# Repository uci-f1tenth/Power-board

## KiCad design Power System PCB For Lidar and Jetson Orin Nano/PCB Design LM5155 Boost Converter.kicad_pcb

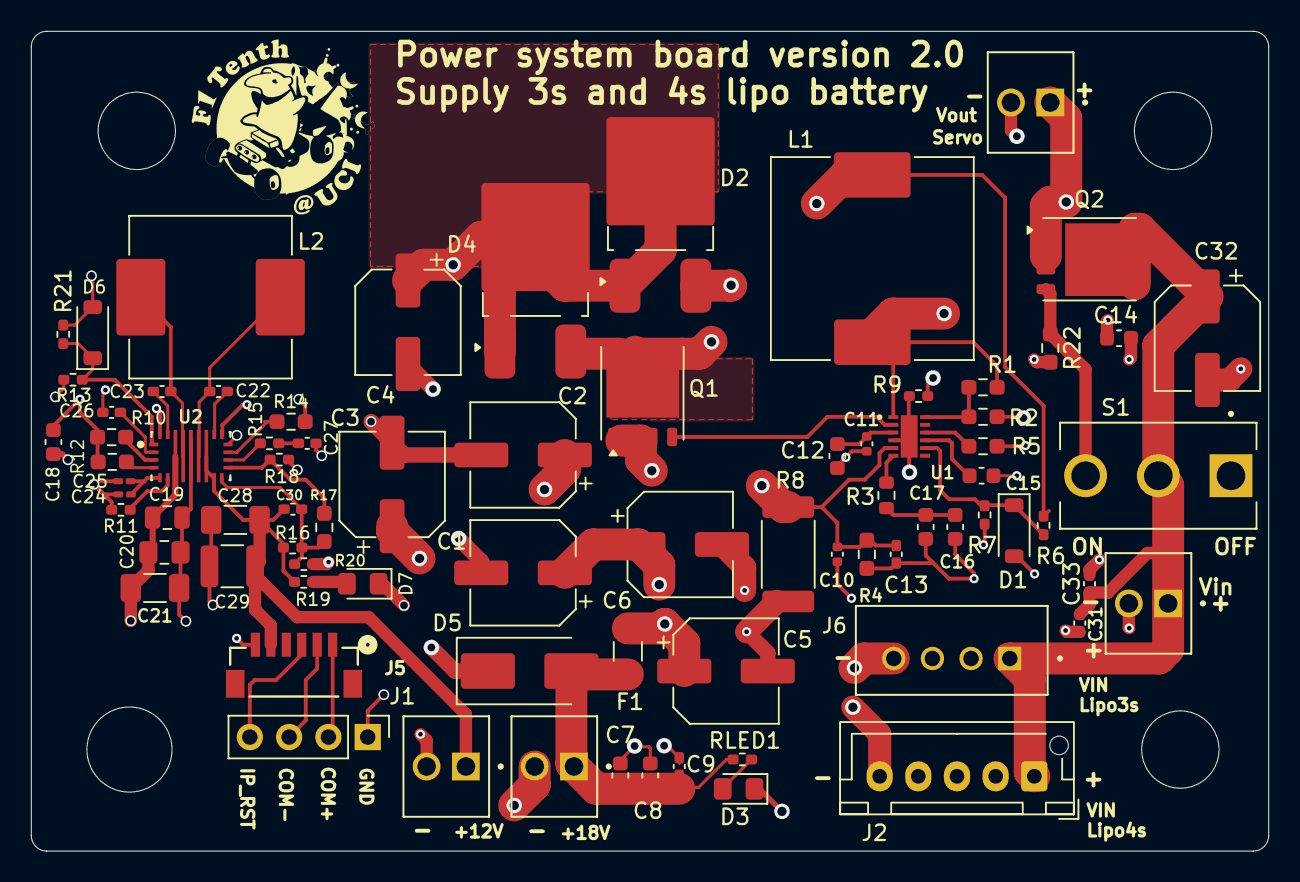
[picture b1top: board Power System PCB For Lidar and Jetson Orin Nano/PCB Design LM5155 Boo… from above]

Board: 4 copper layers, 80.0 x 53.0 mm, 80 parts (0 on the bottom side), 39 nets.

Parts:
+12V, +18V: TB002-500-02BE; TE_282834-2
C1, C2, C3, C4, C5, C6, C32: 100u; CP_Elec_6.3x5.8
C7, C14: 10u; C_0603_1608Metric
C8: 1.5u; C_0603_1608Metric
C9, C22, C23, C30, C31: 0.1u; C_0402_1005Metric_Pad0.74x0.62mm_HandSolder
C10, C11: 1u; C_0402_1005Metric
C12: 0.1u; C_0603_1608Metric
C13: 820p; C_0402_1005Metric_Pad0.74x0.62mm_HandSolder
C15: 0.15u; C_0603_1608Metric
C16: 220n; C_0603_1608Metric
C17: 680p; C_0603_1608Metric
C18: 4.7u; C_0603_1608Metric
C19: 10u; C_0805_2012Metric
C20: 10u; C_0805_2012Metric_Pad1.18x1.45mm_HandSolder
C21, C28: 22u; C_1206_3216Metric_Pad1.33x1.80mm_HandSolder
C24: 470p; C_0201_0603Metric_Pad0.64x0.40mm_HandSolder
C25: 6.8n; C_0201_0603Metric_Pad0.64x0.40mm_HandSolder
C26: 100p; C_0402_1005Metric_Pad0.74x0.62mm_HandSolder
C27, C33: 4.7n; C_0402_1005Metric_Pad0.74x0.62mm_HandSolder
C29: 47u; C_1210_3225Metric
D1: D_Zener; D_SOD-123
D2, D4: D_Schottky; TO-252-2_TabPin1
D3, D7: LED; LED_0805_2012Metric_Pad1.15x1.40mm_HandSolder
D5: D_TVS; D_SMB_Handsoldering
D6: 3.3; D_SOD-123
F1: Fuse; Fuse_1206_3216Metric_Pad1.42x1.75mm_HandSolder
J1: Conn_01x04_Pin; PinHeader_1x04_P2.54mm_Vertical
J2: B5B-XH-A; JST_XH_B5B-XH-AM_1x05_P2.50mm_Vertical
J5: BM06B-SRSS-TBLFSN; CONN_BM06B-SRSS-TB_JST
J6: B4B-XH-A; JST_B4B-XH-A
L1: 10u; L_Vishay_IHLP-5050
L2: 4.7u; L_Vishay_IHLP-4040
Q1, Q2: BSC035N04LS G; Infineon_PG-TDSON-8_6.15x5.15mm
R1: 226k; R_0603_1608Metric_Pad0.98x0.95mm_HandSolder
R2: 64.9k; R_0603_1608Metric_Pad0.98x0.95mm_HandSolder
R3: 1.2k; R_0603_1608Metric
R4: 100; R_0603_1608Metric_Pad0.98x0.95mm_HandSolder
R5: 44.8k; R_0603_1608Metric_Pad0.98x0.95mm_HandSolder
R6: 340k; R_0402_1005Metric_Pad0.72x0.64mm_HandSolder
R7: 20k; R_0402_1005Metric_Pad0.72x0.64mm_HandSolder
R8: 15m; R_2512_6332Metric_Pad1.40x3.35mm_HandSolder
R9: 0; R_0402_1005Metric_Pad0.72x0.64mm_HandSolder
R10, R12, R17, R22: 100k; R_0603_1608Metric_Pad0.98x0.95mm_HandSolder
R11: 50k; R_0402_1005Metric_Pad0.72x0.64mm_HandSolder
R13: 3.3k; R_0402_1005Metric_Pad0.72x0.64mm_HandSolder
R14: 150k; R_0603_1608Metric_Pad0.98x0.95mm_HandSolder
R15: 10k; R_0402_1005Metric_Pad0.72x0.64mm_HandSolder
R16: 10m; R_0402_1005Metric_Pad0.72x0.64mm_HandSolder
R18: 11k; R_0402_1005Metric_Pad0.72x0.64mm_HandSolder
R19: 1k; R_0402_1005Metric_Pad0.72x0.64mm_HandSolder
R20: 3; R_0402_1005Metric_Pad0.72x0.64mm_HandSolder
R21: 698; R_0402_1005Metric_Pad0.72x0.64mm_HandSolder
RLED1: 4k; R_0402_1005Metric_Pad0.72x0.64mm_HandSolder
Ref: LOGO; F1TenthUCILogo
S1: 100SP1T1B4M2QE; SW_100SP1T1B4M2QE
U1: LM5155_DSSR; WSON_551DSSR_TEX
U2: TPS552892RYQR; RYQ0021A-MFG
Vin: TB002-500-02BE; TE_282834-2
Vout: TB002-500-02BE; TE_282834-2

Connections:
/COUT: C1.1, C2.1, C3.1, C4.1, C5.1, C6.1, C19.1, C20.1, C21.1, D2.1 (K), D4.1 (K), F1.1, R13.1, U2.7 (VIN)
/INDUCTOR: C14.1, L1.1, Q2.1 (SOURCE), Q2.2 (SOURCE), Q2.3 (SOURCE), R1.2, R22.2, U1.1 (BIAS), Vout.1
/MOSFET: D2.2 (A), D4.2 (A), L1.2, Q1.5 (DRAIN), R6.1
/RSENSE: C10.1, C13.1, Q1.1 (SOURCE), Q1.2 (SOURCE), Q1.3 (SOURCE), R4.2, R8.1, U1.5 (CS)
/VIN: C31.1, C32.1, C33.1, J2.1, J6.1, Q2.5 (DRAIN), S1.2, Vin.1
/Vout2: +12V.1, C28.1, C29.1, C30.1, J5.5, R16.1, R19.1, U2.11 (VOUT), U2.12 (ISP)
GND: C11.2, C12.2, C13.2, C15.2, C16.2, C17.2, C18.1, C24.2, C25.2, C26.2, C27.2, D1.2 (A), R2.2, R4.1, R5.2, R7.2, R9.1, R11.2, R14.2, R18.2, R20.2, U2.17 (AGND), U2.21 (EXTVCC)
GNDPWR: +12V.2, +18V.2, C1.2, C2.2, C3.2, C4.2, C5.2, C6.2, C7.2, C8.2, C9.2, C10.2, C14.2, C19.2, C20.2, C21.2, C28.2, C29.2, C31.2, C32.2, C33.2, D3.1 (K), D5.1 (A1), D6.2 (A), D7.1 (K), J1.1, J2.5, J5.6, J6.4, R8.2, R9.2, R21.2, U1.4 (PGND), U1.13 (EP), U2.9 (PGND), Vin.2, Vout.2
unnamed: C16.1, C17.1, R3.1
unnamed: C27.1, R15.2
unnamed: D1.1 (K), R6.2, R7.1, U1.8 (FB)
unnamed: D3.2 (A), RLED1.1
unnamed: +18V.1, C7.1, C8.1, C9.1, D5.2 (A2), F1.2, RLED1.2
unnamed: D6.1 (K), R13.2, R21.1, U2.1 (EN_UVLO)
unnamed: D7.2 (A), R19.2
unnamed: J1.2, J5.1
unnamed: J1.3, J5.2
unnamed: J1.4, J5.3
unnamed: Q1.4 (GATE), U1.2 (GATE)
unnamed: Q2.4 (GATE), R22.1, S1.3
unnamed: R3.2, U1.6 (COMP)
unnamed: R5.1, U1.10 (RT)
unnamed: C15.1, U1.9 (SS)
unnamed: R1.1, R2.1, U1.12 (UVLO/SYNC)
unnamed: C11.1, C12.1, U1.3 (VCC)
unnamed: C23.2, U2.20 (BOOT1)
unnamed: C22.2, U2.19 (BOOT2)
unnamed: R12.2, U2.4 (CC_N)
unnamed: R14.1, U2.16 (CDC)
unnamed: R15.1, U2.15 (COMP)
unnamed: C24.1, C25.1, U2.5 (DITH_SYNC)
unnamed: R17.2, R18.1, U2.14 (FB)
unnamed: R11.1, U2.6 (FSW)
unnamed: C30.2, R16.2, R17.1, R20.1, U2.13 (ISN)
unnamed: C26.1, U2.2 (MODE)
unnamed: R10.2, U2.3 (PG)
unnamed: C23.1, L2.1, U2.8 (SW1)
unnamed: C22.1, L2.2, U2.10 (SW2)
unnamed: C18.2, R10.1, R12.1, U2.18 (VCC)

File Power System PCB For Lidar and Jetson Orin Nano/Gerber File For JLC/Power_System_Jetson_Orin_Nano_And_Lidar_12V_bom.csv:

Designator,Footprint,Quantity,Value,LCSC Part #
"+12V, +18V, VIN, VOUT",TE_282834-2,4,TB002-500-02BE,
"C1, C2, C3, C32, C4, C5, C6",CP_Elec_6.3x5.8,7,100u,
"C10, C11",0402,2,1u,
C12,0603,1,0.1u,
C13,0402,1,820p,
"C14, C7",0603,2,10u,
C15,0603,1,0.15u,
C16,0603,1,220n,
C17,0603,1,680p,
C18,0603,1,4.7u,
"C19, C20",0805,2,10u,
"C21, C28",1206,2,22u,
"C22, C23, C30, C31, C9",0402,5,0.1u,
C24,0201,1,470p,
C25,0201,1,6.8n,
C26,0402,1,100p,
"C27, C33",0402,2,4.7n,
C29,1210,1,47u,
C8,0603,1,1.5u,
D1,D_SOD-123,1,D_Zener,
"D2, D4",TO-252-2_TabPin1,2,D_Schottky,
"D3, D7",0805,2,LED,
D5,D_SMB_Handsoldering,1,D_TVS,
D6,D_SOD-123,1,3.3,
F1,1206,1,Fuse,
J1,PinHeader_1x04_P2.54mm_Vertical,1,Conn_01x04_Pin,
J2,JST_XH_B5B-XH-AM_1x05_P2.50mm_Vertical,1,B5B-XH-A,
J5,CONN_BM06B-SRSS-TB_JST,1,BM06B-SRSS-TBLFSN,
J6,JST_B4B-XH-A,1,B4B-XH-A,
L1,L_Vishay_IHLP-5050,1,10u,
L2,L_Vishay_IHLP-4040,1,4.7u,
"Q1, Q2",Infineon_PG-TDSON-8_6.15x5.15mm,2,BSC035N04LS G,
R1,0603,1,226k,
"R10, R12, R17, R22",0603,4,100k,
R11,0402,1,50k,
R13,0402,1,3.3k,
R14,0603,1,150k,
R15,0402,1,10k,
R16,0402,1,10m,
R18,0402,1,11k,
R19,0402,1,1k,
R2,0603,1,64.9k,
R20,0402,1,3,
R21,0402,1,698,
R3,0603,1,1.2k,
R4,0603,1,100,
R5,0603,1,44.8k,
R6,0402,1,340k,
R7,0402,1,20k,
R8,2512,1,15m,
R9,0402,1,0,
RLED1,0402,1,4k,
S1,SW_100SP1T1B4M2QE,1,100SP1T1B4M2QE,
U1,WSON_551DSSR_TEX,1,LM5155_DSSR,
U2,RYQ0021A-MFG,1,TPS552892RYQR,

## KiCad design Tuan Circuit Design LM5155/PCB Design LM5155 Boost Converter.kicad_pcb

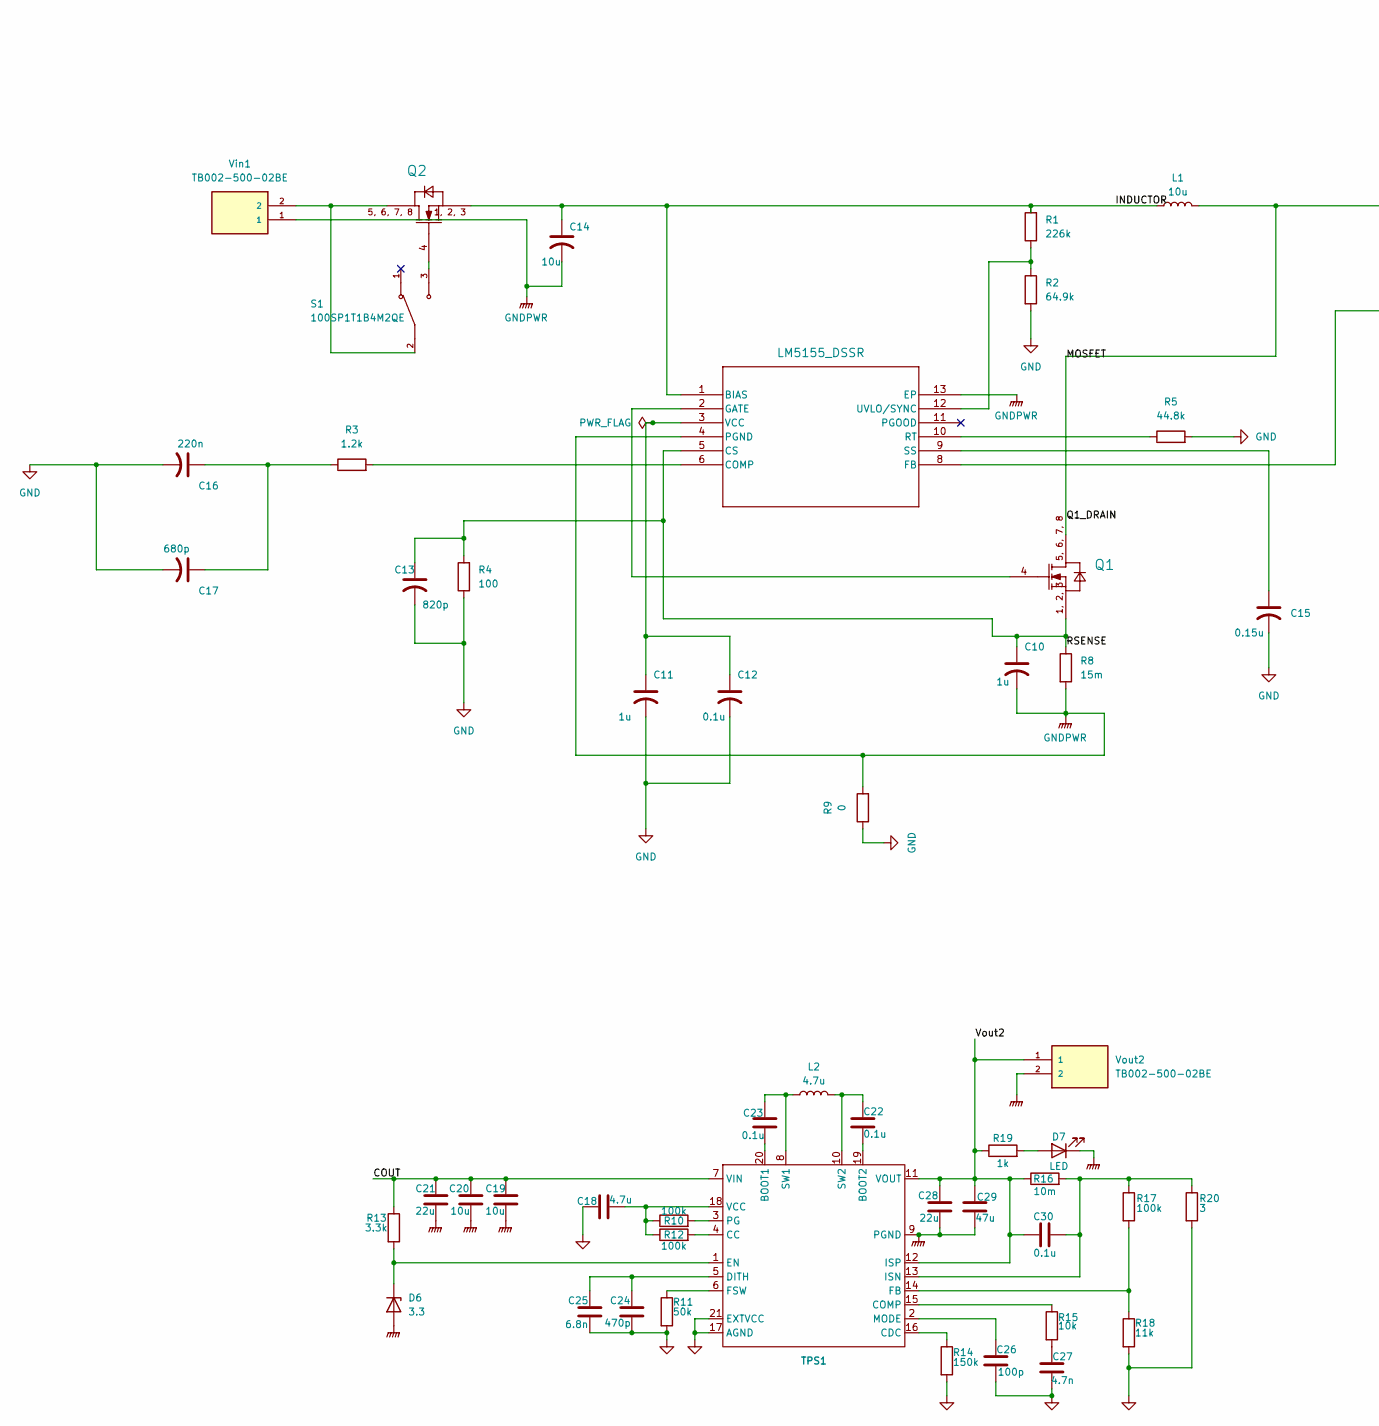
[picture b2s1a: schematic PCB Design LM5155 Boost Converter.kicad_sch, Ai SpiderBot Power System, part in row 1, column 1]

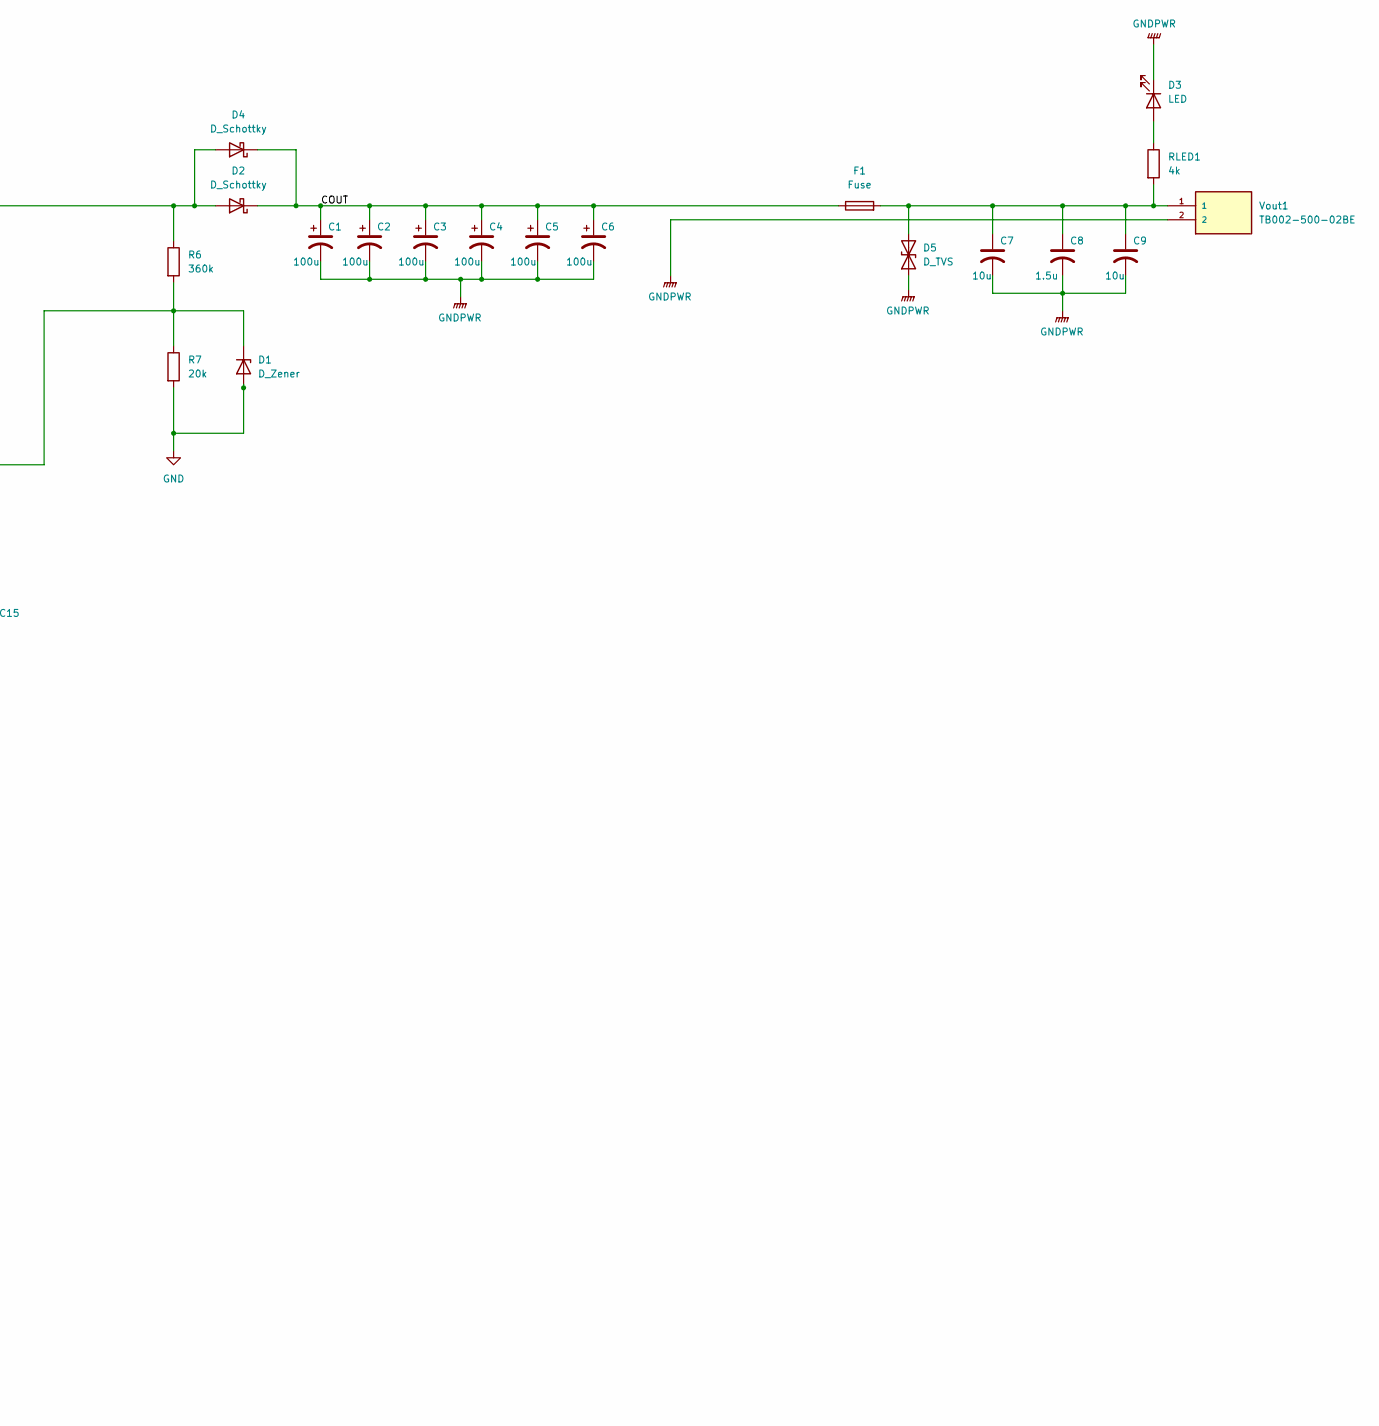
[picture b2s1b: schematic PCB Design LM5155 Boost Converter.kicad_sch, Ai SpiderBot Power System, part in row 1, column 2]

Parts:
C1, C2, C3, C4, C5, C6: 100u; CP_Elec_6.3x5.8
C7, C9, C14: 10u; C_0603_1608Metric
C8: 1.5u; C_0603_1608Metric
C10, C11: 1u; C_0402_1005Metric
C12: 0.1u; C_0603_1608Metric
C13: 820p; C_0402_1005Metric_Pad0.74x0.62mm_HandSolder
C15: 0.15u; C_0603_1608Metric
C16: 220n; C_0603_1608Metric
C17: 680p; C_0603_1608Metric
C18: 4.7u; C_0603_1608Metric
C19: 10u; C_0805_2012Metric
C20: 10u; C_0805_2012Metric_Pad1.18x1.45mm_HandSolder
C21, C28: 22u; C_1206_3216Metric_Pad1.33x1.80mm_HandSolder
C22, C23, C30: 0.1u; C_0402_1005Metric_Pad0.74x0.62mm_HandSolder
C24: 470p; C_0201_0603Metric_Pad0.64x0.40mm_HandSolder
C25: 6.8n; C_0201_0603Metric_Pad0.64x0.40mm_HandSolder
C26: 100p; C_0402_1005Metric_Pad0.74x0.62mm_HandSolder
C27: 4.7n; C_0402_1005Metric_Pad0.74x0.62mm_HandSolder
C29: 47u; C_1210_3225Metric
D1: D_Zener; D_SOD-123
D2, D4: D_Schottky; TO-252-2_TabPin1
D3, D7: LED; LED_0805_2012Metric_Pad1.15x1.40mm_HandSolder
D5: D_TVS; D_SMB_Handsoldering
D6: 3.3; D_SOD-123
F1: Fuse; Fuse_1206_3216Metric_Pad1.42x1.75mm_HandSolder
L1: 10u; L_Vishay_IHLP-5050
L2: 4.7u; L_Vishay_IHLP-4040
Q1, Q2: BSC035N04LS G; INF-PG-TDSON-8; ManufacturerPartNumber BSC035N04LS G
R1: 226k; R_0603_1608Metric_Pad0.98x0.95mm_HandSolder
R2: 64.9k; R_0603_1608Metric_Pad0.98x0.95mm_HandSolder
R3: 1.2k; R_0603_1608Metric
R4: 100; R_0603_1608Metric_Pad0.98x0.95mm_HandSolder
R5: 44.8k; R_0603_1608Metric_Pad0.98x0.95mm_HandSolder
R6: 360k; R_0402_1005Metric_Pad0.72x0.64mm_HandSolder
R7: 20k; R_0402_1005Metric_Pad0.72x0.64mm_HandSolder
R8: 15m; R_2512_6332Metric_Pad1.40x3.35mm_HandSolder
R9: 0; R_0402_1005Metric_Pad0.72x0.64mm_HandSolder
R10, R12, R17: 100k; R_0603_1608Metric_Pad0.98x0.95mm_HandSolder
R11: 50k; R_0402_1005Metric_Pad0.72x0.64mm_HandSolder
R13: 3.3k; R_0402_1005Metric_Pad0.72x0.64mm_HandSolder
R14: 150k; R_0603_1608Metric_Pad0.98x0.95mm_HandSolder
R15: 10k; R_0402_1005Metric_Pad0.72x0.64mm_HandSolder
R16: 10m; R_0402_1005Metric_Pad0.72x0.64mm_HandSolder
R18: 11k; R_0402_1005Metric_Pad0.72x0.64mm_HandSolder
R19: 1k; R_0402_1005Metric_Pad0.72x0.64mm_HandSolder
R20: 3; R_0402_1005Metric_Pad0.72x0.64mm_HandSolder
RLED1: 4k; R_0402_1005Metric_Pad0.72x0.64mm_HandSolder
S1: 100SP1T1B4M2QE; SW_100SP1T1B4M2QE; PARTREV E
TPS1: CONV_TPS552892RYQR
U1: LM5155_DSSR; WSON_551DSSR_TEX
Vin1: TB002-500-02BE; CUI_TB002-500-02BE
Vout1, Vout2: TB002-500-02BE; CUI_TB002-500-02BE

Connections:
/COUT: C1.1, C2.1, C3.1, C4.1, C5.1, C6.1, C19.1, C20.1, C21.1, D2.1 (K), D4.1 (K), F1.1, R13.1, TPS1.7 (VIN)
/INDUCTOR: C14.1, L1.1, Q2.1 (SOURCE), Q2.2 (SOURCE), Q2.3 (SOURCE), R1.2, U1.1 (BIAS)
/MOSFET: D2.2 (A), D4.2 (A), L1.2, Q1.5 (DRAIN), Q1.6 (DRAIN), Q1.7 (DRAIN), Q1.8 (DRAIN), R6.1
/RSENSE: C10.1, C13.1, Q1.1 (SOURCE), Q1.2 (SOURCE), Q1.3 (SOURCE), R4.2, R8.1, U1.5 (CS)
/Vout2: C28.1, C29.1, C30.1, R16.1, R19.1, TPS1.11 (VOUT), TPS1.12 (ISP), Vout2.1
GND: C11.2, C12.2, C13.2, C15.2, C16.2, C17.2, C18.1, C24.2, C25.2, C26.2, C27.2, D1.2 (A), R2.2, R4.1, R5.2, R7.2, R9.1, R11.2, R14.2, R18.2, R20.2, TPS1.17 (AGND), TPS1.21 (EXTVCC)
GNDPWR: C1.2, C2.2, C3.2, C4.2, C5.2, C6.2, C7.2, C8.2, C9.2, C10.2, C14.2, C19.2, C20.2, C21.2, C28.2, C29.2, D3.1 (K), D5.1 (A1), D6.2 (A), D7.1 (K), R8.2, R9.2, TPS1.9 (PGND), U1.4 (PGND), U1.13 (EP), Vin1.1, Vout1.2, Vout2.2; also elsewhere on the board
unnamed: C16.1, C17.1, R3.1
unnamed: C27.1, R15.2
unnamed: D1.1 (K), R6.2, R7.1, U1.8 (FB)
unnamed: D3.2 (A), RLED1.1
unnamed 11: C7.1, C8.1, C9.1, D5.2 (A2), F1.2, RLED1.2, Vout1.1; also elsewhere on the board
unnamed: D6.1 (K), R13.2, TPS1.1 (EN)
unnamed: D7.2 (A), R19.2
unnamed: Q1.4 (GATE), U1.2 (GATE)
unnamed 15: Q2.5 (DRAIN), Q2.6 (DRAIN), Q2.7 (DRAIN), Q2.8 (DRAIN), S1.2, Vin1.2; also elsewhere on the board
unnamed: Q2.4 (GATE), S1.3
unnamed: C23.2, TPS1.20 (BOOT1)
unnamed: C22.2, TPS1.19 (BOOT2)
unnamed: R12.2, TPS1.4 (CC)
unnamed: R14.1, TPS1.16 (CDC)
unnamed: R15.1, TPS1.15 (COMP)
unnamed: C24.1, C25.1, TPS1.5 (DITH)
unnamed: R17.2, R18.1, TPS1.14 (FB)
unnamed: R11.1, TPS1.6 (FSW)
unnamed: C30.2, R16.2, R17.1, R20.1, TPS1.13 (ISN)
unnamed: C26.1, TPS1.2 (MODE)
unnamed: R10.2, TPS1.3 (PG)
unnamed: C23.1, L2.1, TPS1.8 (SW1)
unnamed: C22.1, L2.2, TPS1.10 (SW2)
unnamed: C18.2, R10.1, R12.1, TPS1.18 (VCC)
unnamed: R3.2, U1.6 (COMP)
unnamed: R5.1, U1.10 (RT)
unnamed: C15.1, U1.9 (SS)
unnamed: R1.1, R2.1, U1.12 (UVLO/SYNC)
unnamed: C11.1, C12.1, U1.3 (VCC)

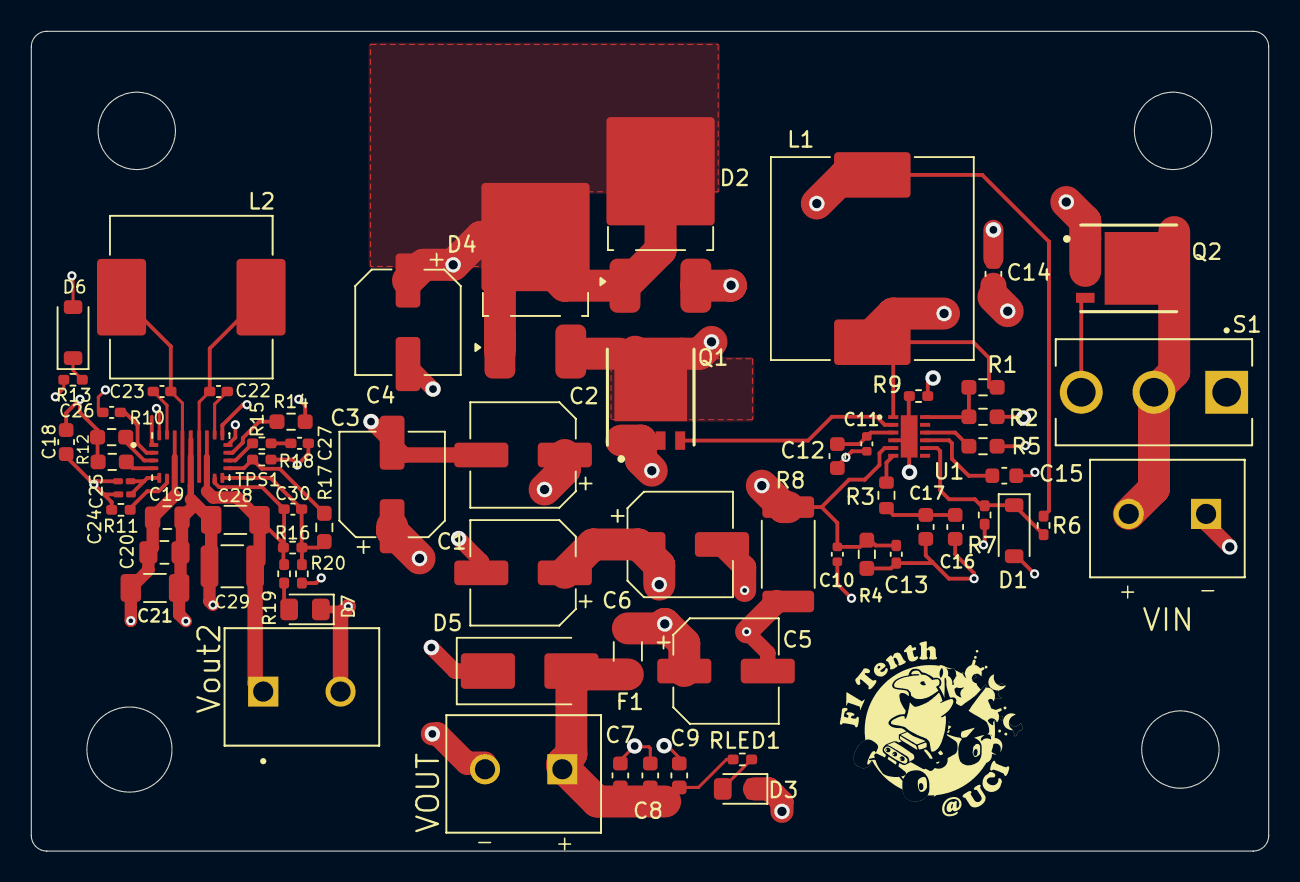
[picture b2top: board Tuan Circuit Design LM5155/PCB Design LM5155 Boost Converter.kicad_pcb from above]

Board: 4 copper layers, 80.0 x 53.0 mm, 70 parts (0 on the bottom side), 36 nets.

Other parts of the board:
Ref: LOGO; F1TenthUCILogo
VIN: TB002-500-02BE; CUI_TB002-500-02BE
VOUT: TB002-500-02BE; CUI_TB002-500-02BE

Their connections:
GNDPWR: VIN.1, VOUT.2; also elsewhere on the board
unnamed 11: VOUT.1; also elsewhere on the board
unnamed 15: VIN.2; also elsewhere on the board

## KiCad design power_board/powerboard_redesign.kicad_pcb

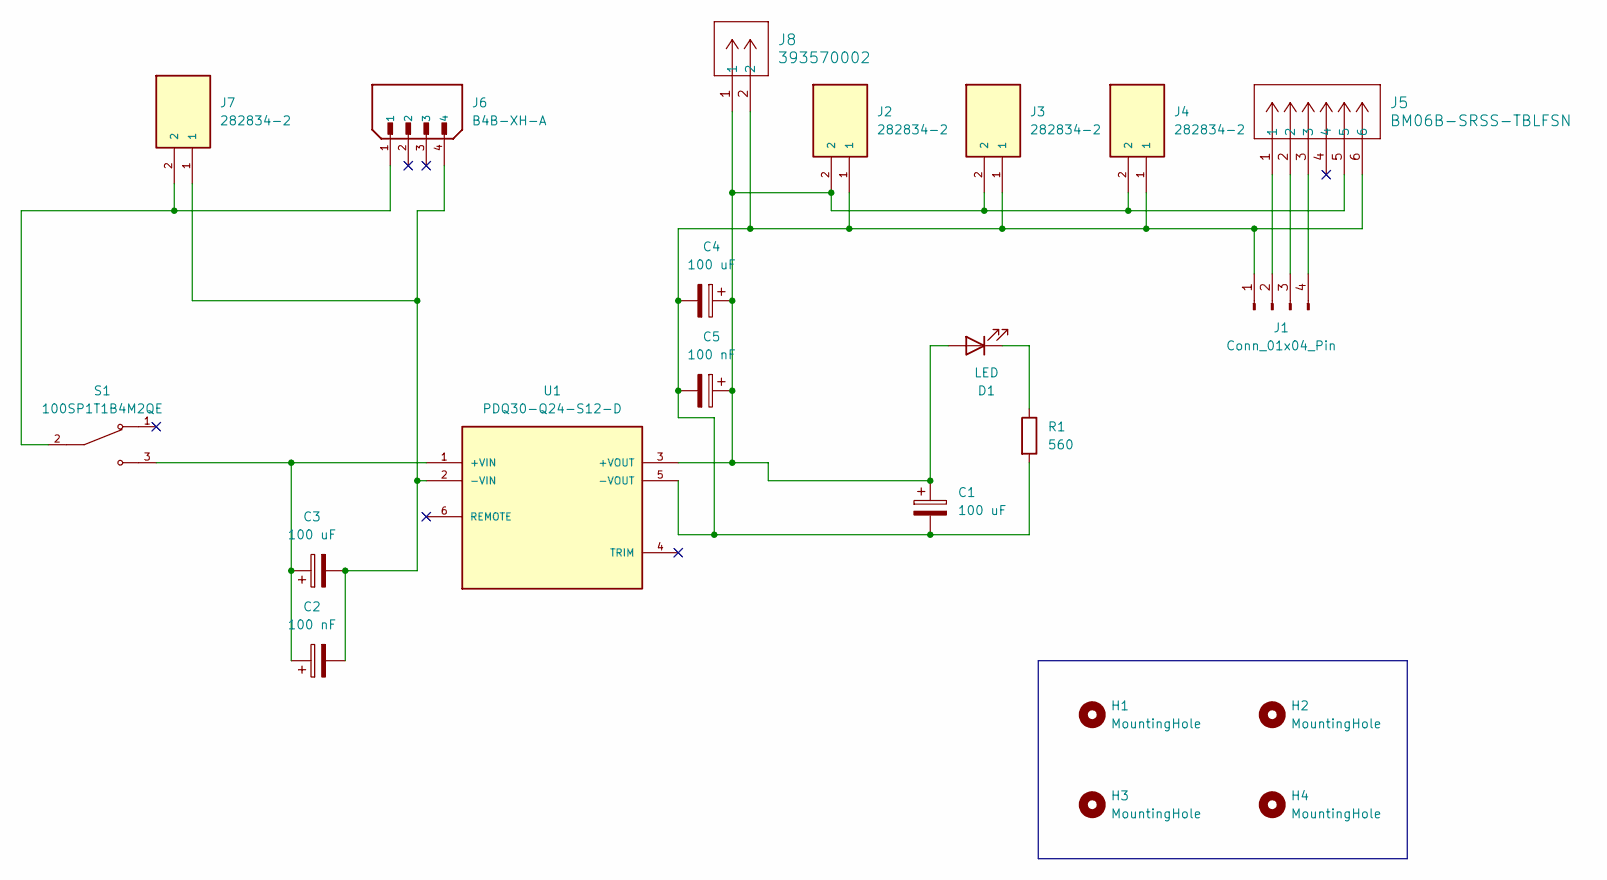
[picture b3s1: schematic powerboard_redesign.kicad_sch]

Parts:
C1, C3, C4: 100 uF; CP_Radial_D8.0mm_P3.50mm
C2, C5: 100 nF; CP_Radial_D8.0mm_P3.50mm
D1: LED; LED_D3.0mm
H1, H2, H3, H4: MountingHole; MountingHole_5.5mm
J1: Conn_01x04_Pin; PinHeader_1x04_P2.54mm_Vertical
J2, J3, J4, J7: 282834-2; TE_282834-2; PARTREV D
J5: BM06B-SRSS-TBLFSN; CONN_BM06B-SRSS-TB_JST
J6: B4B-XH-A; JST_B4B-XH-A; PARTREV 7/4/21
J8: 393570002; CONN_SD-39357-001_02P_MOL
R1: 560; R_Axial_DIN0207_L6.3mm_D2.5mm_P10.16mm_Horizontal
S1: 100SP1T1B4M2QE; SW_100SP1T1B4M2QE; PARTREV E
U1: PDQ30-Q24-S12-D; CONV_PDQ30-Q24-S12-D; PARTREV 1.0

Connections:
unnamed: C1.1, C4.1, C5.1, D1.2 (A), J2.2, J3.2, J4.2, J5.5, J8.1, U1.3 (+VOUT)
unnamed: D1.1 (K), R1.1
unnamed: C1.2, C4.2, C5.2, J1.1, J2.1, J3.1, J4.1, J5.6, J8.2, R1.2, U1.5 (-VOUT)
unnamed: J1.2, J5.1
unnamed: J1.3, J5.2
unnamed: J1.4, J5.3
unnamed: J6.1, J7.2, S1.2
unnamed: C2.1, C3.1, S1.3, U1.1 (+VIN)
unnamed: C2.2, C3.2, J6.4, J7.1, U1.2 (-VIN)

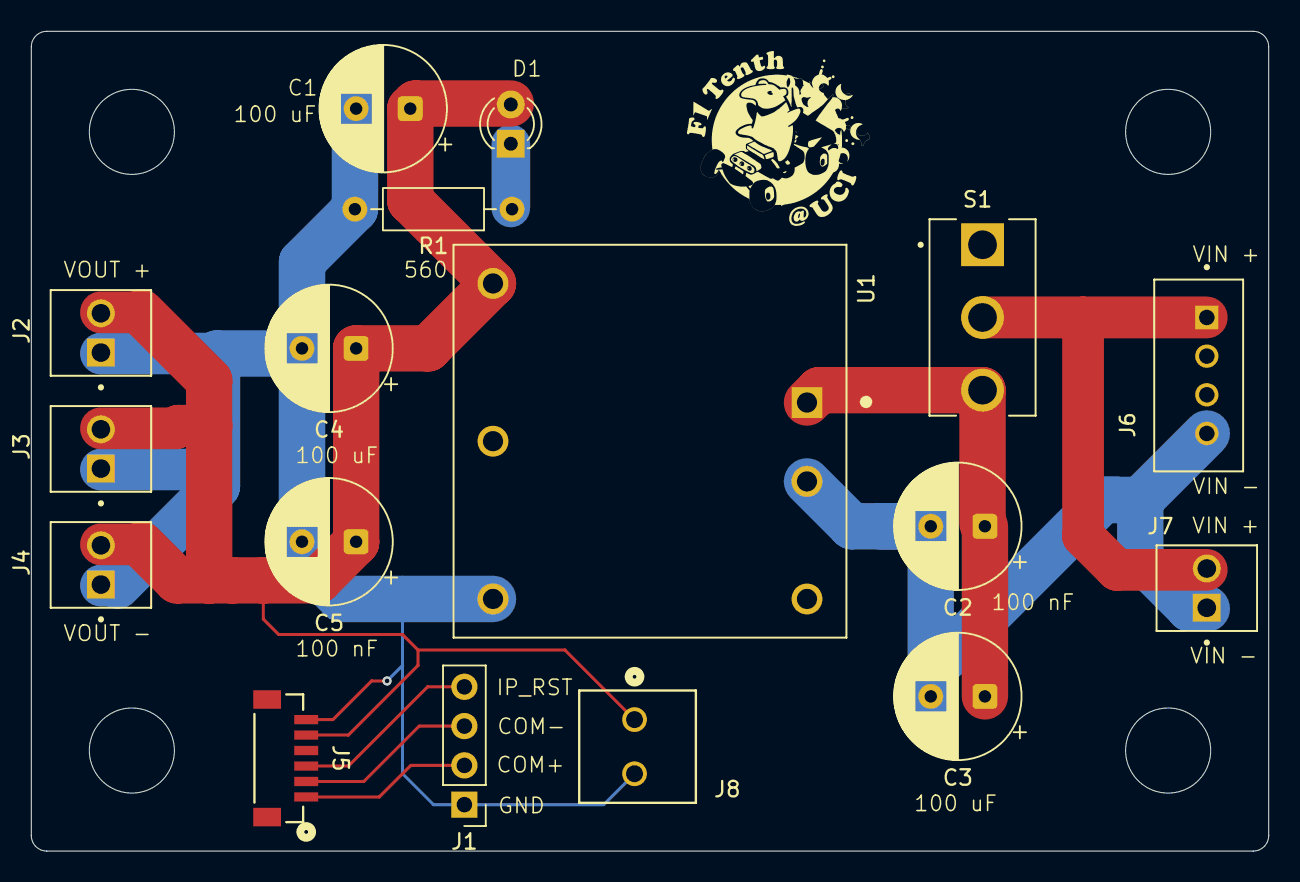
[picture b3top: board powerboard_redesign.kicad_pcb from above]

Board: 2 copper layers, 80.0 x 53.0 mm, 22 parts (0 on the bottom side), 9 nets.

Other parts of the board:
Ref: LOGO; F1TenthUCILogo

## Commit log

2025-11-07 GNU V3.0
2025-11-07 current work on redesign
2025-11-08 redesign re-upload
    evaluation from Bradley would be appreciated
2025-11-10 newest iteration
    need to add footprints for pcb
2025-11-10 current directory with PDQ30-Q24-S12-D
    PDQ30-Q24-S12-D footprint added, need to add 1x4 connector for battery and other foot prints, need to figure out two capacitor values
2026-01-06 Version One Done
    still need to resize some traces, and fix some overlaps stated in KiCAD DRC
2026-01-08 Traces fixed
    Ready for print on Version One
2026-01-08 Gerber and Excellon Files
    Added the Gerber and Excellon Files and a file with the bill of materials and pick and place files (CPL, I think).
2026-01-15 updated bom for digikey
2026-02-12 Updated V2 Powerboard
    Fixed some connections, check if correct, still need to add some features for redundancy and safety
2026-03-29 Added Project Specific Library configs for Footprints and Symbols
2026-03-29 Added BM06B-SRSS-TB Connector
    For powering LiDAR module, reference: https://github.com/AlistairKeiller/Lidar-Power-Adapter
2026-03-29 Added BM06B-SRSS-TB to Schematic
    No wires yet, need to know LiDAR module pins
2026-03-31 Adjusted other parts to use Project Specific Library Paths
2026-03-31 Added Datasheet link for BM06-SRSS-TB Connector
2026-04-02 Added connections to BM06B-SRSS-TB
2026-04-02 Added Footprint and Symbol files for Battery Connector
2026-04-02 Added B4B-XH-A (Battery) Connector to Project Specific Library
2026-04-02 Added 3D Step file to Battery Connector Footprint
2026-04-02 Added Step file for BM06B-SRSS-TB Connector
2026-04-02 Added Step file to BM06B-SRSS-TB Footprint
2026-04-02 Replaced Screw Terminal with B4B-XH-A for Battery
2026-04-02 Updated PCB with new connectors
2026-04-09 Updated schematic and PCB for V3
    Added 4-pin connector for LiDAR connector
2026-04-09 Powerboard V3 Files
2026-04-23 Replaced D12 Buck Converter with S12 Buck Converter
    Great Job Allen!
2026-04-23 Updated Powerboard to have S12 instead of D12 + Added 2 Terminal Block on Battery Side
2026-04-23 Updated PCB with S12 Buck Converter + extra screw terminal block on Battery side
2026-04-24 Added 28 awg terminal block for LiDAR
2026-04-24 Added 28 awg terminal block to schematic
    This is for LiDAR connection power wires as another option instead of JST 6-pin connector
2026-04-24 Updated 28 awg block with 3D model
2026-04-24 Added .gitignore for KiCAD temporary files
2026-05-10 Version 5
    Initial Commit
2026-05-10 Updated the LIDAR Power Supply
2026-05-10 Completed Schematic for LIDAR Power
2026-05-11 Updated PCB Schematic
    Moved the LM5155 to the right
2026-05-13 Routing for TPS Module
2026-05-13 Updated .gitignore
2026-05-13 Removed backups
2026-05-14 PCB Traces
2026-05-14 added box
2026-05-14 Added circle
2026-05-14 2 Layer to 4 Layer PCB
2026-05-14 Updated Schematic
2026-05-14 Upload file for my own branch
2026-05-14 Circuit after fix with 4 layer PCB
2026-05-14 Error Fix
2026-05-14 Fix Update
2026-05-14 reaarange schematic
2026-05-14 File contain LM5155 and terminal symbol, 3D, and 2D view
2026-05-14 Fix small issue on connection and add resistor
2026-05-14 Add resistor
2026-05-14 Update PRL
2026-05-16 Add switch
2026-05-16 Update 3D model
2026-05-16 component list purchase
2026-05-16 Update voltage protection (TVS and Fuse)
2026-05-16 Update New List Buying
2026-05-16 Name Change
2026-05-16 fix name layout
2026-05-18 Update silkscreen
2026-05-20 File Update
2026-05-20 Finish Product
2026-05-20 Adjust some wire
2026-05-20 adjust vias
2026-05-20 Adjust wire
2026-05-21 Update Silkscreen Backboard
2026-05-21 Adjust some stuff
2026-05-21 Update silkscreen back
2026-05-21 Gerber File
